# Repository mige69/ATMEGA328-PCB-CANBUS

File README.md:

# ATMEGA328-PCB-CANBUS
eagle autodesk ATMEGA328 PCB CANBUS

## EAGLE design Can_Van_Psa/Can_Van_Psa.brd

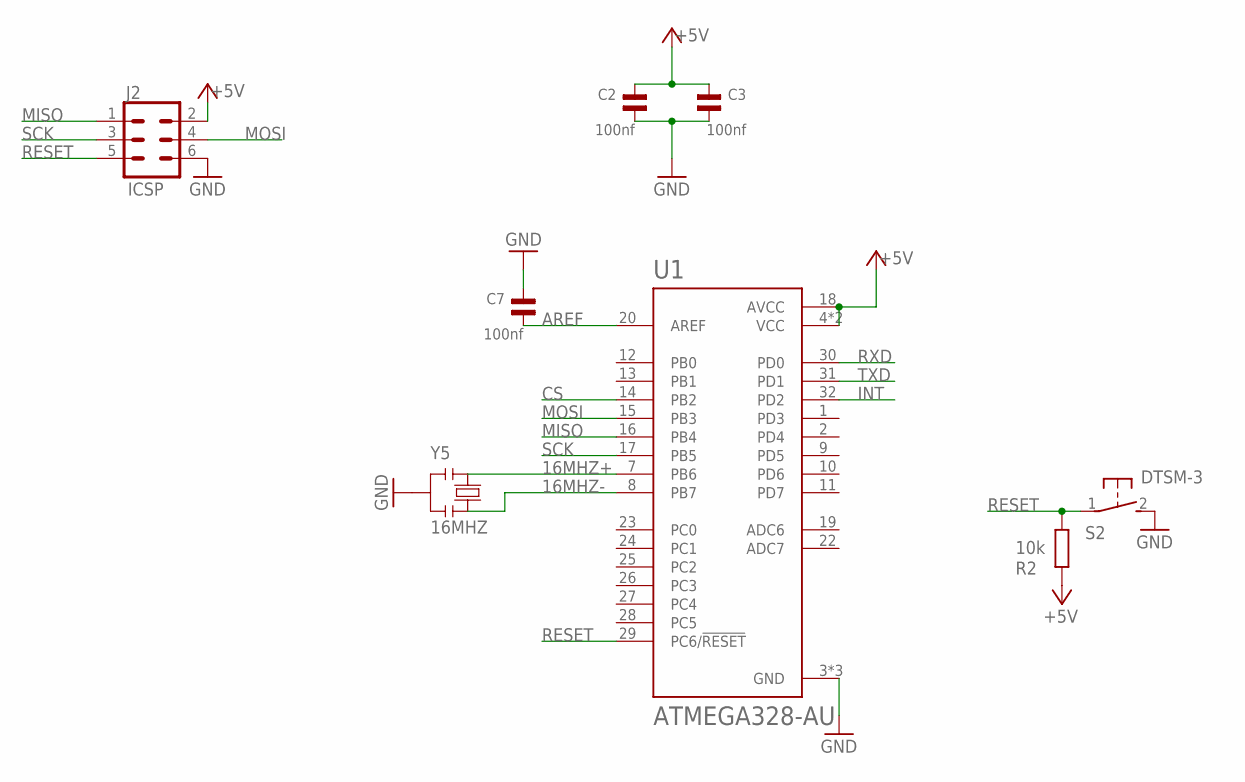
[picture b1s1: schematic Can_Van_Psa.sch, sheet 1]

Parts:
C2, C3, C7: 100nf; 0805
J2: ICSP; 2X3
R2: 10k; R0805
S2: DTSM-3
U1: ATMEGA328-AU; QFP80P900X900X120-32N
Y5: 16MHZ; CSTCE16M0V53

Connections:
16MHZ+: U1.7 (PB6), Y5.1
16MHZ-: U1.8 (PB7), Y5.3
+5V: C2.2, C3.2, J2.2, R2.2, U1.4 (VCC), U1.6 (VCC), U1.18 (AVCC); also elsewhere on the board
AREF: C7.1, U1.20 (AREF)
CS: U1.14 (PB2); also elsewhere on the board
GND: C2.1, C3.1, C7.2, J2.6, S2.2, U1.3 (GND), U1.5 (GND), U1.21 (GND), Y5.2; also elsewhere on the board
INT: U1.32 (PD2); also elsewhere on the board
MISO: J2.1, U1.16 (PB4); also elsewhere on the board
MOSI: J2.4, U1.15 (PB3); also elsewhere on the board
RESET: J2.5, R2.1, S2.1, U1.29 (PC6/!RESET); also elsewhere on the board
RXD: U1.30 (PD0); also elsewhere on the board
SCK: J2.3, U1.17 (PB5); also elsewhere on the board
TXD: U1.31 (PD1); also elsewhere on the board

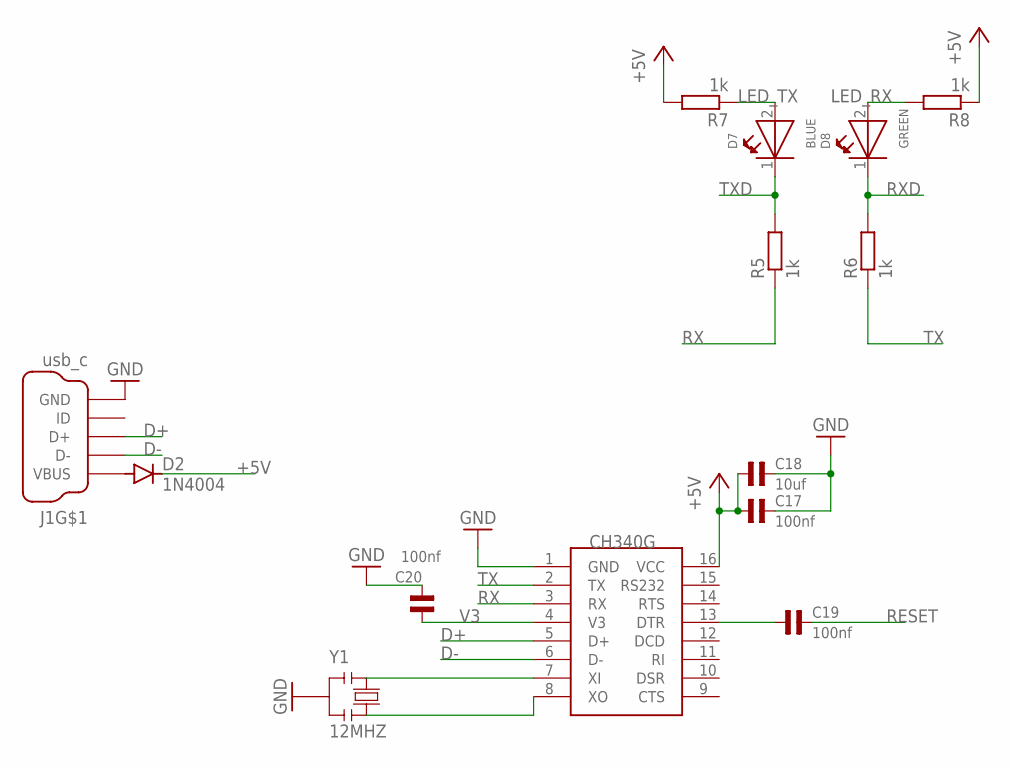
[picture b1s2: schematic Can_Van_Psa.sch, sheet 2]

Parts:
C17, C19, C20: 100nf; 0805
C18: 10uf; 0805
D2: 1N4004; DO214AA
D7: BLUE; 0805
D8: GREEN; 0805
J1: usb_c; MOLEX_0548190519
R5, R6, R7, R8: 1k; R0805
U$1: CH340G; SOIC16
Y1: 12MHZ; CSTCE16M0V53

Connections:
+5V: C17.1, C18.1, D2.C, R7.2, R8.1, U$1.16 (VCC); also elsewhere on the board
D+: J1.3 (D+), J1.8 (D+), U$1.5 (D+)
D-: J1.2 (D-), J1.7 (D-), U$1.6 (D-)
GND: C17.2, C18.2, C20.2, J1.5 (GND), J1.10 (GND), U$1.1 (GND), Y1.2; also elsewhere on the board
LED_RX: D8.2 (A), R8.2
LED_TX: D7.2 (A), R7.1
unnamed: D2.A, J1.1 (VBUS), J1.6 (VBUS)
unnamed: U$1.7 (XI), Y1.1
unnamed: C19.1, U$1.13 (DTR)
unnamed: U$1.8 (XO), Y1.3
RESET: C19.2; also elsewhere on the board
RX: R5.1, U$1.3 (RX)
RXD: D8.1 (K), R6.2; also elsewhere on the board
TX: R6.1, U$1.2 (TX)
TXD: D7.1 (K), R5.2; also elsewhere on the board
V3: C20.1, U$1.4 (V3)

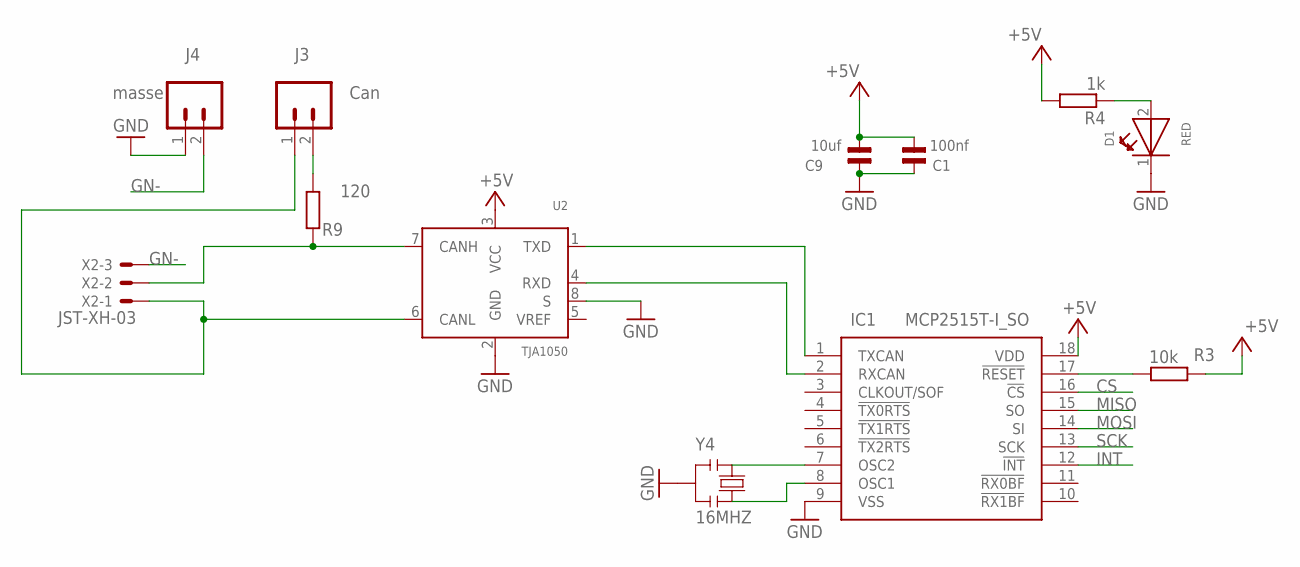
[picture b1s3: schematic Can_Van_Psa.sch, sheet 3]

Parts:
C1: 100nf; 0805
C9: 10uf; 0805
D1: RED; 0805
IC1: MCP2515T-I_SO; SOIC127P1030X265-18N
J3: Can; 1X02
J4: masse; 1X02
R3: 10k; R0805
R4: 1k; R0805
R9: 120; R0805
U2: TJA1050; SOT96-1
X2: JST-XH-03; JST-XH-03-PACKAGE-LONG-PAD
Y4: 16MHZ; CSTCE16M0V53

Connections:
+5V: C1.2, C9.2, IC1.18 (VDD), R3.2, R4.2, U2.3 (VCC); also elsewhere on the board
CS: IC1.16 (!CS); also elsewhere on the board
GN-: J4.2, X2.3
GND: C1.1, C9.1, D1.1 (K), IC1.9 (VSS), J4.1, U2.2 (GND), U2.8 (S), Y4.2; also elsewhere on the board
INT: IC1.12 (!INT); also elsewhere on the board
MISO: IC1.15 (SO); also elsewhere on the board
MOSI: IC1.14 (SI); also elsewhere on the board
unnamed: IC1.1 (TXCAN), U2.1 (TXD)
unnamed: IC1.2 (RXCAN), U2.4 (RXD)
unnamed: J3.2, R9.1
unnamed: IC1.17 (!RESET), R3.1
unnamed: D1.2 (A), R4.1
unnamed: R9.2, U2.7 (CANH), X2.2
unnamed: J3.1, U2.6 (CANL), X2.1
unnamed: IC1.7 (OSC2), Y4.1
unnamed: IC1.8 (OSC1), Y4.3
SCK: IC1.13 (SCK); also elsewhere on the board

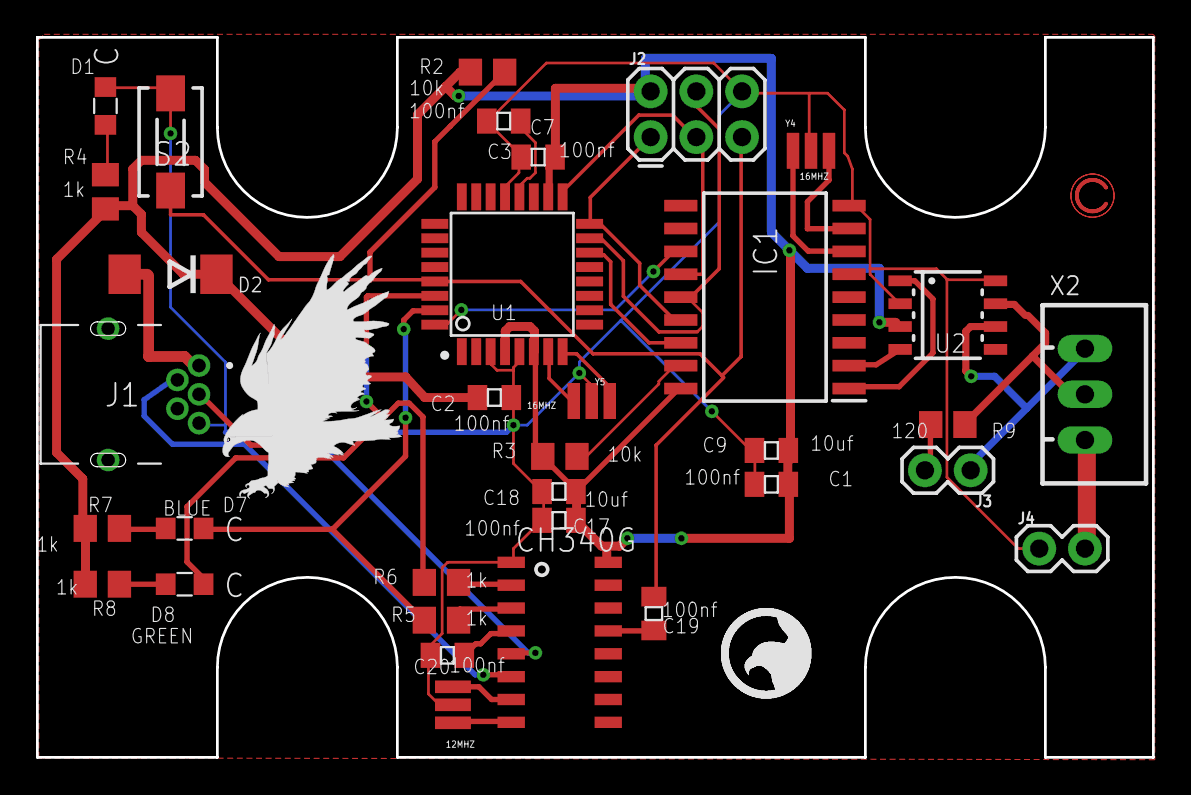
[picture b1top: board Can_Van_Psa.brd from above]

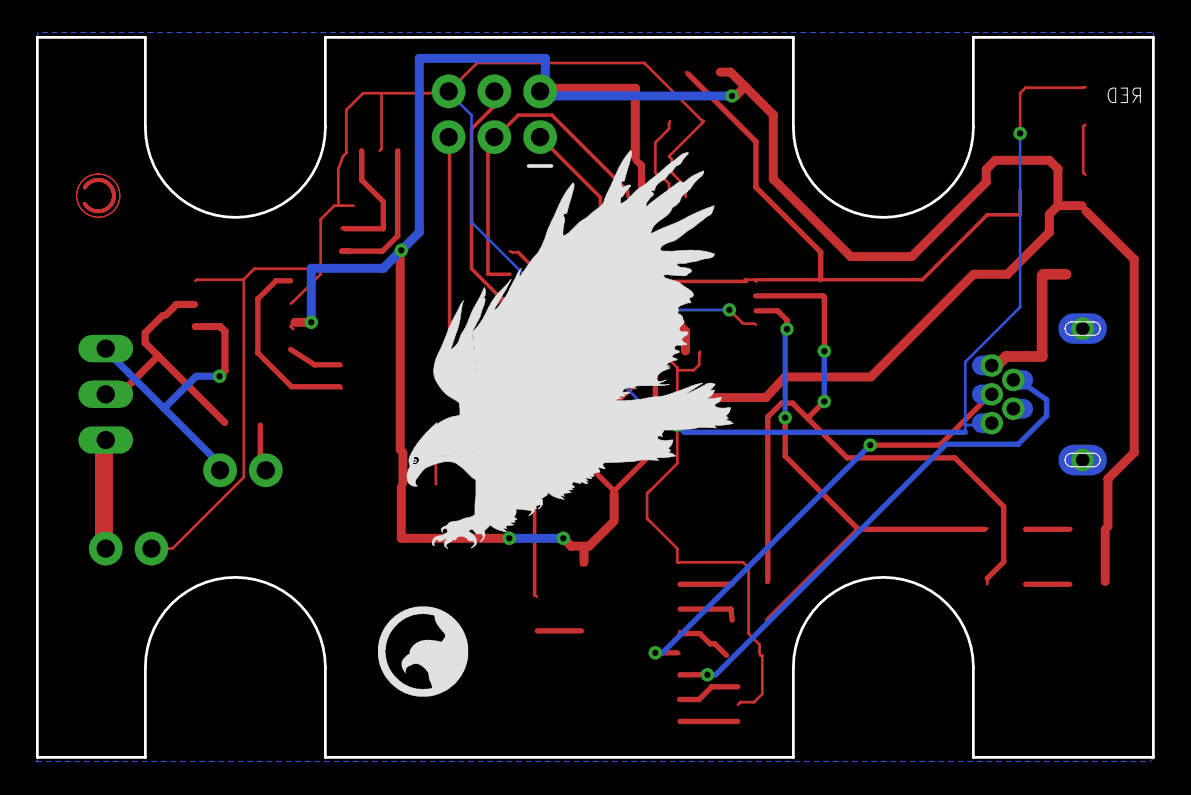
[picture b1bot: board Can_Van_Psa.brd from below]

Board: 2 copper layers, 62.0 x 40.0 mm, 42 parts (3 on the bottom side), 34 nets.

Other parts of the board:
U$2, U$3, U$10: CS-2016-LOGO-5MM
U$5, U$9: EAGLE-PLC-15MM
U$6, U$7: COPYRIGHT-2.4MM
U$8: EAGLE-PLC-10MM

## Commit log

2025-03-12 Create USER
2025-03-12 Update USER

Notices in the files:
parts and their libraries:
Wurth_Elektronik_Optoelectronics_rev15b: Copyright: Würth Elektronik
SparkFun-Connectors: Licensing: Creative Commons ShareAlike 4.0 International - https://creativecommons.org/licenses/by-sa/4.0
